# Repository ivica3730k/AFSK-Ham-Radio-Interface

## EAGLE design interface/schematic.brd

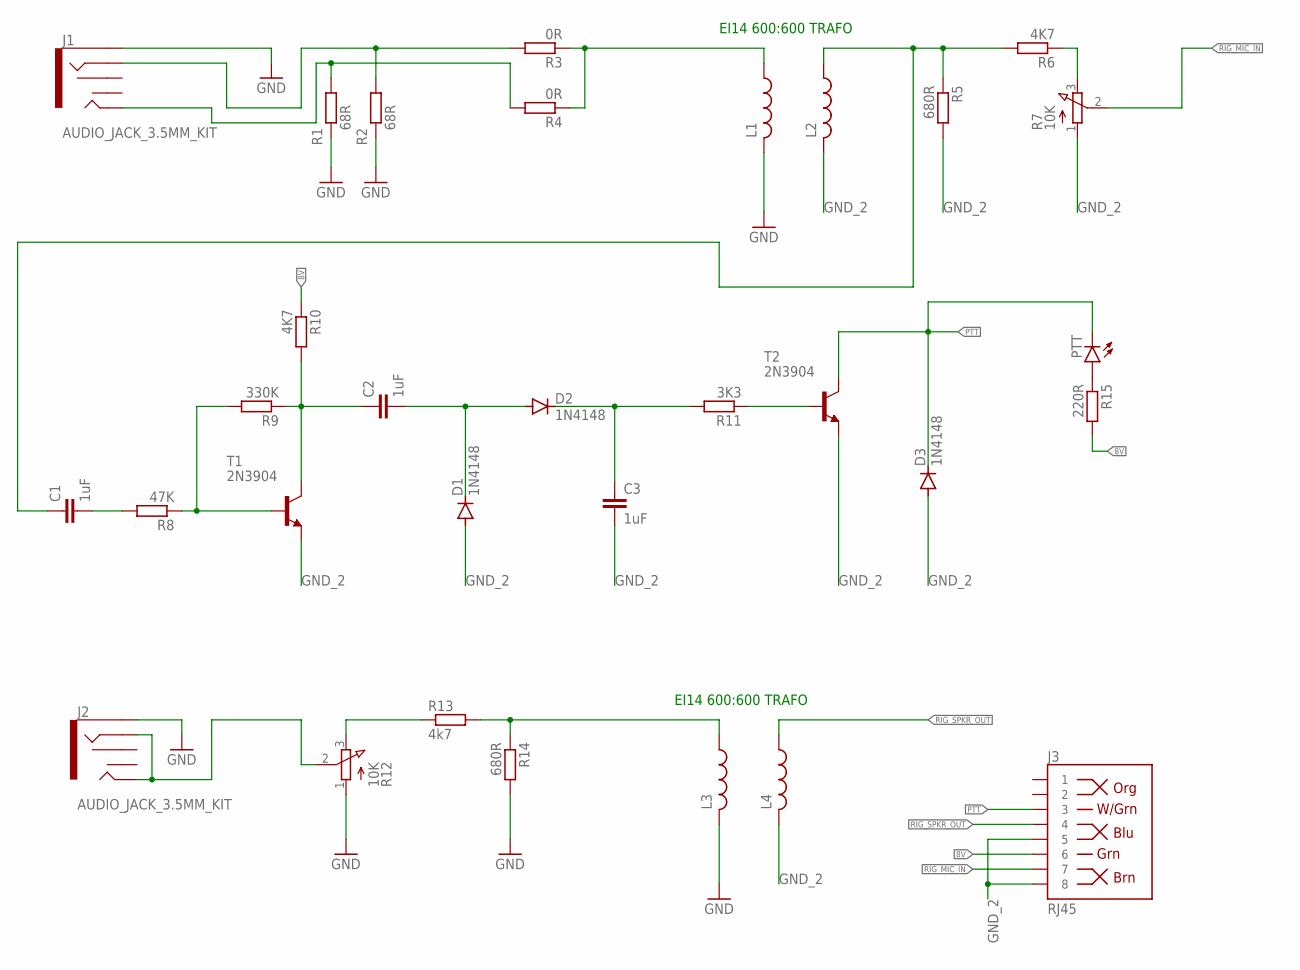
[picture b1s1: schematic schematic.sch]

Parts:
C1, C2, C3: 1uF; C025-030X050
D1, D2, D3: 1N4148; DO35-7
J1, J2: AUDIO_JACK_3.5MM_KIT; AUDIO-JACK-KIT
J3: RJ45; RJ45-8
L1, L2, L3, L4: L-US0204/5; 0204/5
PTT: LED5MM
R1, R2: 68R; 0207/10
R3, R4: 0R; R0805
R5, R14: 680R; 0207/10
R6, R10: 4K7; 0207/10
R7, R12: 10K; 3RP/1610N
R8: 47K; 0207/10
R9: 330K; 0207/10
R11: 3K3; 0207/10
R13: 4k7; 0207/10
R15: 220R; 0207/10
T1, T2: 2N3904; TO92

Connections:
8V: J3.6, R10.1, R15.2
GND: J1.SLEEVE, J2.SLEEVE, L1.2, L3.2, R1.1, R2.1, R12.1 (A), R14.2
GND_2: C3.2, D1.A, D3.A, J3.5, J3.8, L2.2, L4.2, R5.2, R7.1 (A), T1.3 (E), T2.3 (E)
unnamed: J1.RING, R2.2, R3.2
unnamed: J1.TIP, R1.2, R4.2
unnamed: R12.3 (E), R13.1
unnamed: J2.RING, J2.TIP, R12.2 (S)
unnamed: R6.1, R7.3 (E)
unnamed: PTT.A, R15.1
unnamed: L3.1, R13.2, R14.1
unnamed: C1.2, R8.2
unnamed: C2.1, R9.1, R10.2, T1.1 (C)
unnamed: R8.1, R9.2, T1.2 (B)
unnamed: C2.2, D1.C, D2.A
unnamed: C3.1, D2.C, R11.2
unnamed: R11.1, T2.2 (B)
unnamed: C1.1, L2.1, R5.1, R6.2
unnamed: L1.1, R3.1, R4.1
PTT: D3.C, J3.3, PTT.K (C), T2.1 (C)
RIG_MIC_IN: J3.7, R7.2 (S)
RIG_SPKR_OUT: J3.4, L4.1

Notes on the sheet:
EI14 600:600 TRAFO

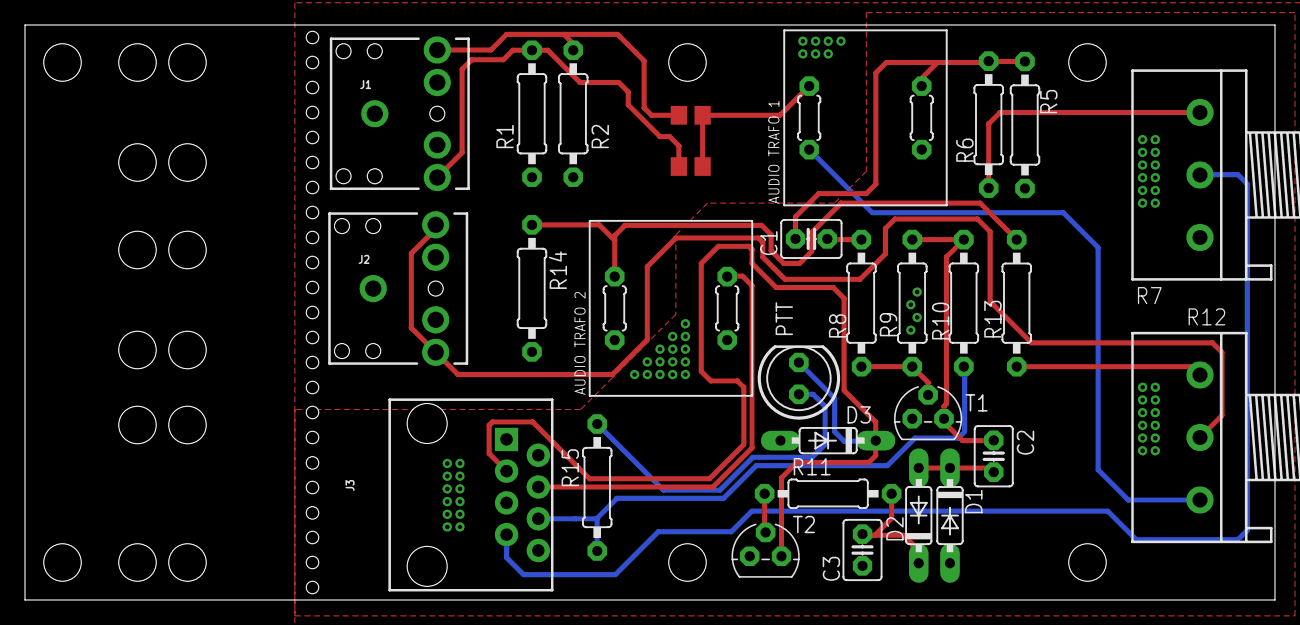
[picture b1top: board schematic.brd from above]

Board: 2 copper layers, 100.0 x 46.0 mm, 31 parts (0 on the bottom side), 21 nets.

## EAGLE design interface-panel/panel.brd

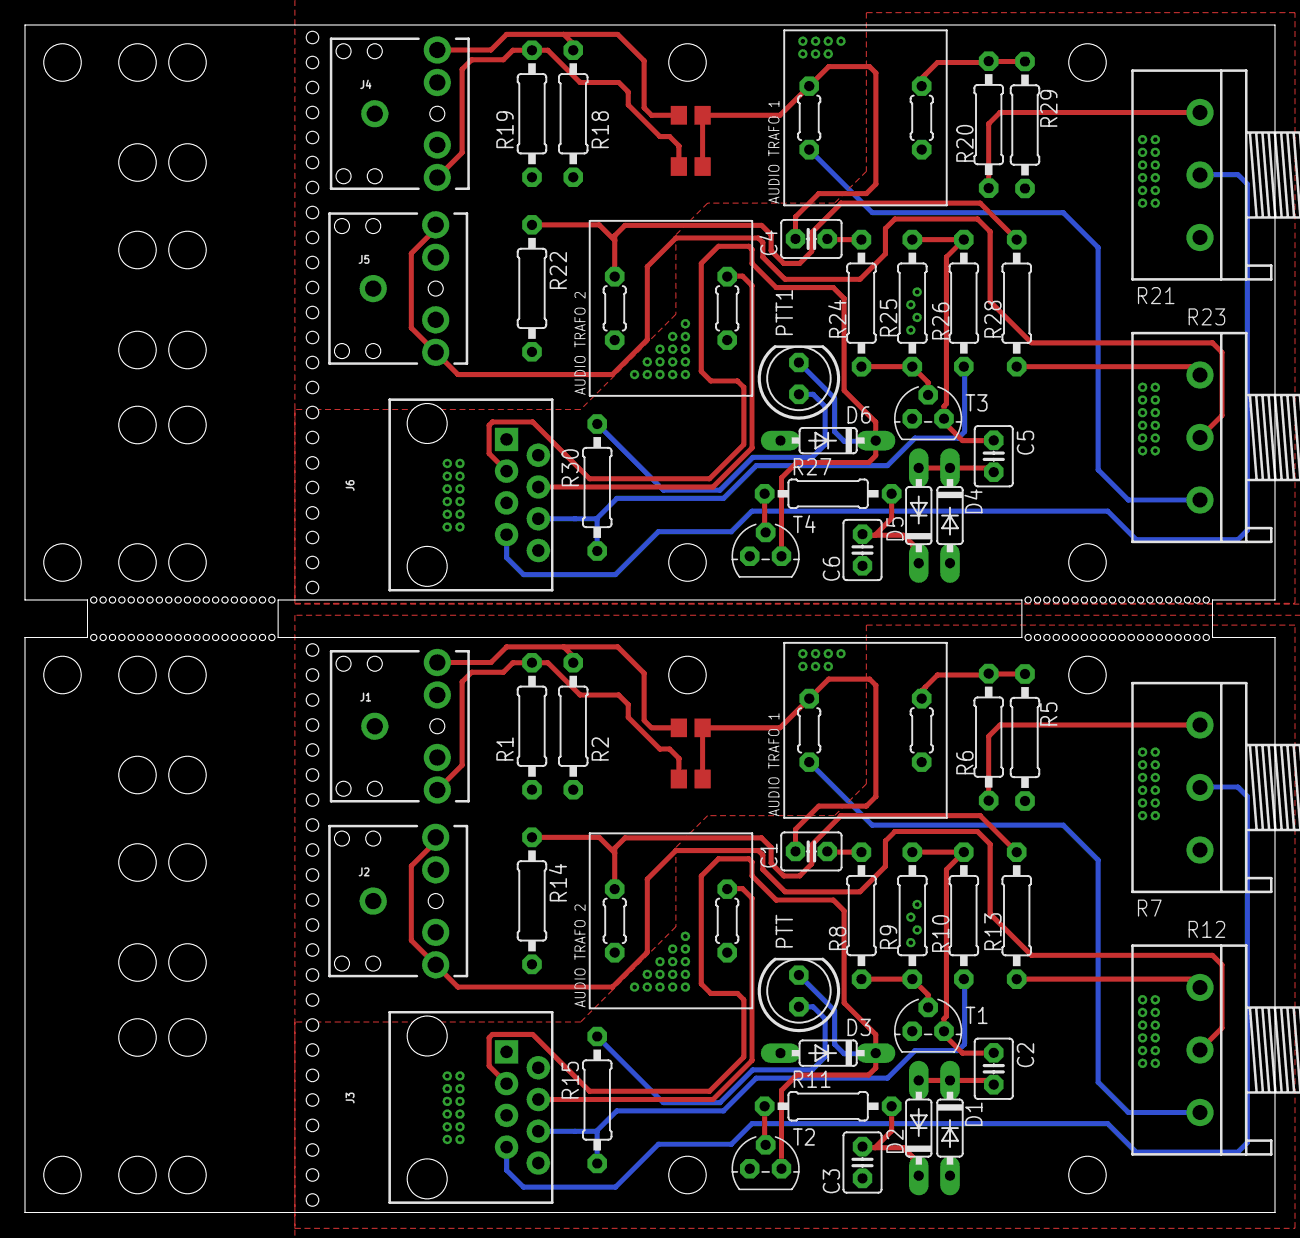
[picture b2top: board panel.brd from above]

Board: 2 copper layers, 100.0 x 95.0 mm, 62 parts (0 on the bottom side), 42 nets.

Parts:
C1, C2, C3, C4, C5, C6: 1uF; C025-030X050
D1, D2, D3, D4, D5, D6: 1N4148; DO35-7
J1, J2, J4, J5: AUDIO_JACK_3.5MM_KIT; AUDIO-JACK-KIT
J3, J6: RJ45; RJ45-8
L1, L2, L3, L4, L5, L6, L7, L8: 0204/5
PTT, PTT1: LED5MM
R1, R2, R18, R19: 68R; 0207/10
R3, R4, R16, R17: 0R; R0805
R5, R14, R22, R29: 680R; 0207/10
R6, R10, R20, R26: 4K7; 0207/10
R7, R12, R21, R23: 10K; 3RP/1610N
R8, R24: 47K; 0207/10
R9, R25: 330K; 0207/10
R11, R27: 3K3; 0207/10
R13, R28: 4k7; 0207/10
R15, R30: 220R; 0207/10
T1, T2, T3, T4: 2N3904; TO92

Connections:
8V: J3.6, R10.1, R15.2
8V1: J6.6, R26.1, R30.2
GND: J1.SLEEVE, J2.SLEEVE, L1.2, L3.2, R1.1, R2.1, R12.1, R14.2
GND1: J4.SLEEVE, J5.SLEEVE, L5.2, L7.2, R18.1, R19.1, R22.2, R23.1
GND_1: C6.2, D4.A, D6.A, J6.5, J6.8, L6.2, L8.2, R21.1, R29.2, T3.3, T4.3
GND_2: C3.2, D1.A, D3.A, J3.5, J3.8, L2.2, L4.2, R5.2, R7.1, T1.3, T2.3
unnamed: J1.RING, R2.2, R3.2
unnamed: J1.TIP, R1.2, R4.2
unnamed: R12.3, R13.1
unnamed: J2.RING, J2.TIP, R12.2
unnamed: R6.1, R7.3
unnamed: PTT.A, R15.1
unnamed: L3.1, R13.2, R14.1
unnamed: L2.1, R5.1, R6.2
unnamed: C1.2, R8.2
unnamed: C2.1, R9.1, R10.2, T1.1
unnamed: R8.1, R9.2, T1.2
unnamed: C2.2, D1.C, D2.A
unnamed: C3.1, D2.C, R11.2
unnamed: R11.1, T2.2
unnamed: C1.1, L1.1, R3.1, R4.1
unnamed: L6.1, R20.2, R29.1
unnamed: J4.RING, R16.2, R18.2
unnamed: J4.TIP, R17.2, R19.2
unnamed: J5.RING, J5.TIP, R23.2
unnamed: L7.1, R22.1, R28.2
unnamed: C4.2, R24.2
unnamed: R24.1, R25.2, T3.2
unnamed: C5.1, R25.1, R26.2, T3.1
unnamed: C5.2, D4.C, D5.A
unnamed: R27.1, T4.2
unnamed: C6.1, D5.C, R27.2
unnamed: C4.1, L5.1, R16.1, R17.1
unnamed: R20.1, R21.3
unnamed: R23.3, R28.1
unnamed: PTT1.A, R30.1
PTT: D3.C, J3.3, PTT.K, T2.1
PTT1: D6.C, J6.3, PTT1.K, T4.1
RIG_MIC_IN: J3.7, R7.2
RIG_MIC_IN1: J6.7, R21.2
RIG_SPKR_OUT: J3.4, L4.1
RIG_SPKR_OUT1: J6.4, L8.1

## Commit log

2020-11-08 Uploaded .gitignore file for EAGLE PCB
2020-11-08 Uploaded project files
2020-11-08 Added decals
2020-11-08 Uploaded gerber files and cam job file
2020-11-08 Updated gerber files
2020-11-09 Updated single board file
2020-12-27 Fixed component numbering to match ordered boards

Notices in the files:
parts and their libraries:
SparkFun-Connectors: Licensing: Creative Commons ShareAlike 4.0 International - https://creativecommons.org/licenses/by-sa/4.0
